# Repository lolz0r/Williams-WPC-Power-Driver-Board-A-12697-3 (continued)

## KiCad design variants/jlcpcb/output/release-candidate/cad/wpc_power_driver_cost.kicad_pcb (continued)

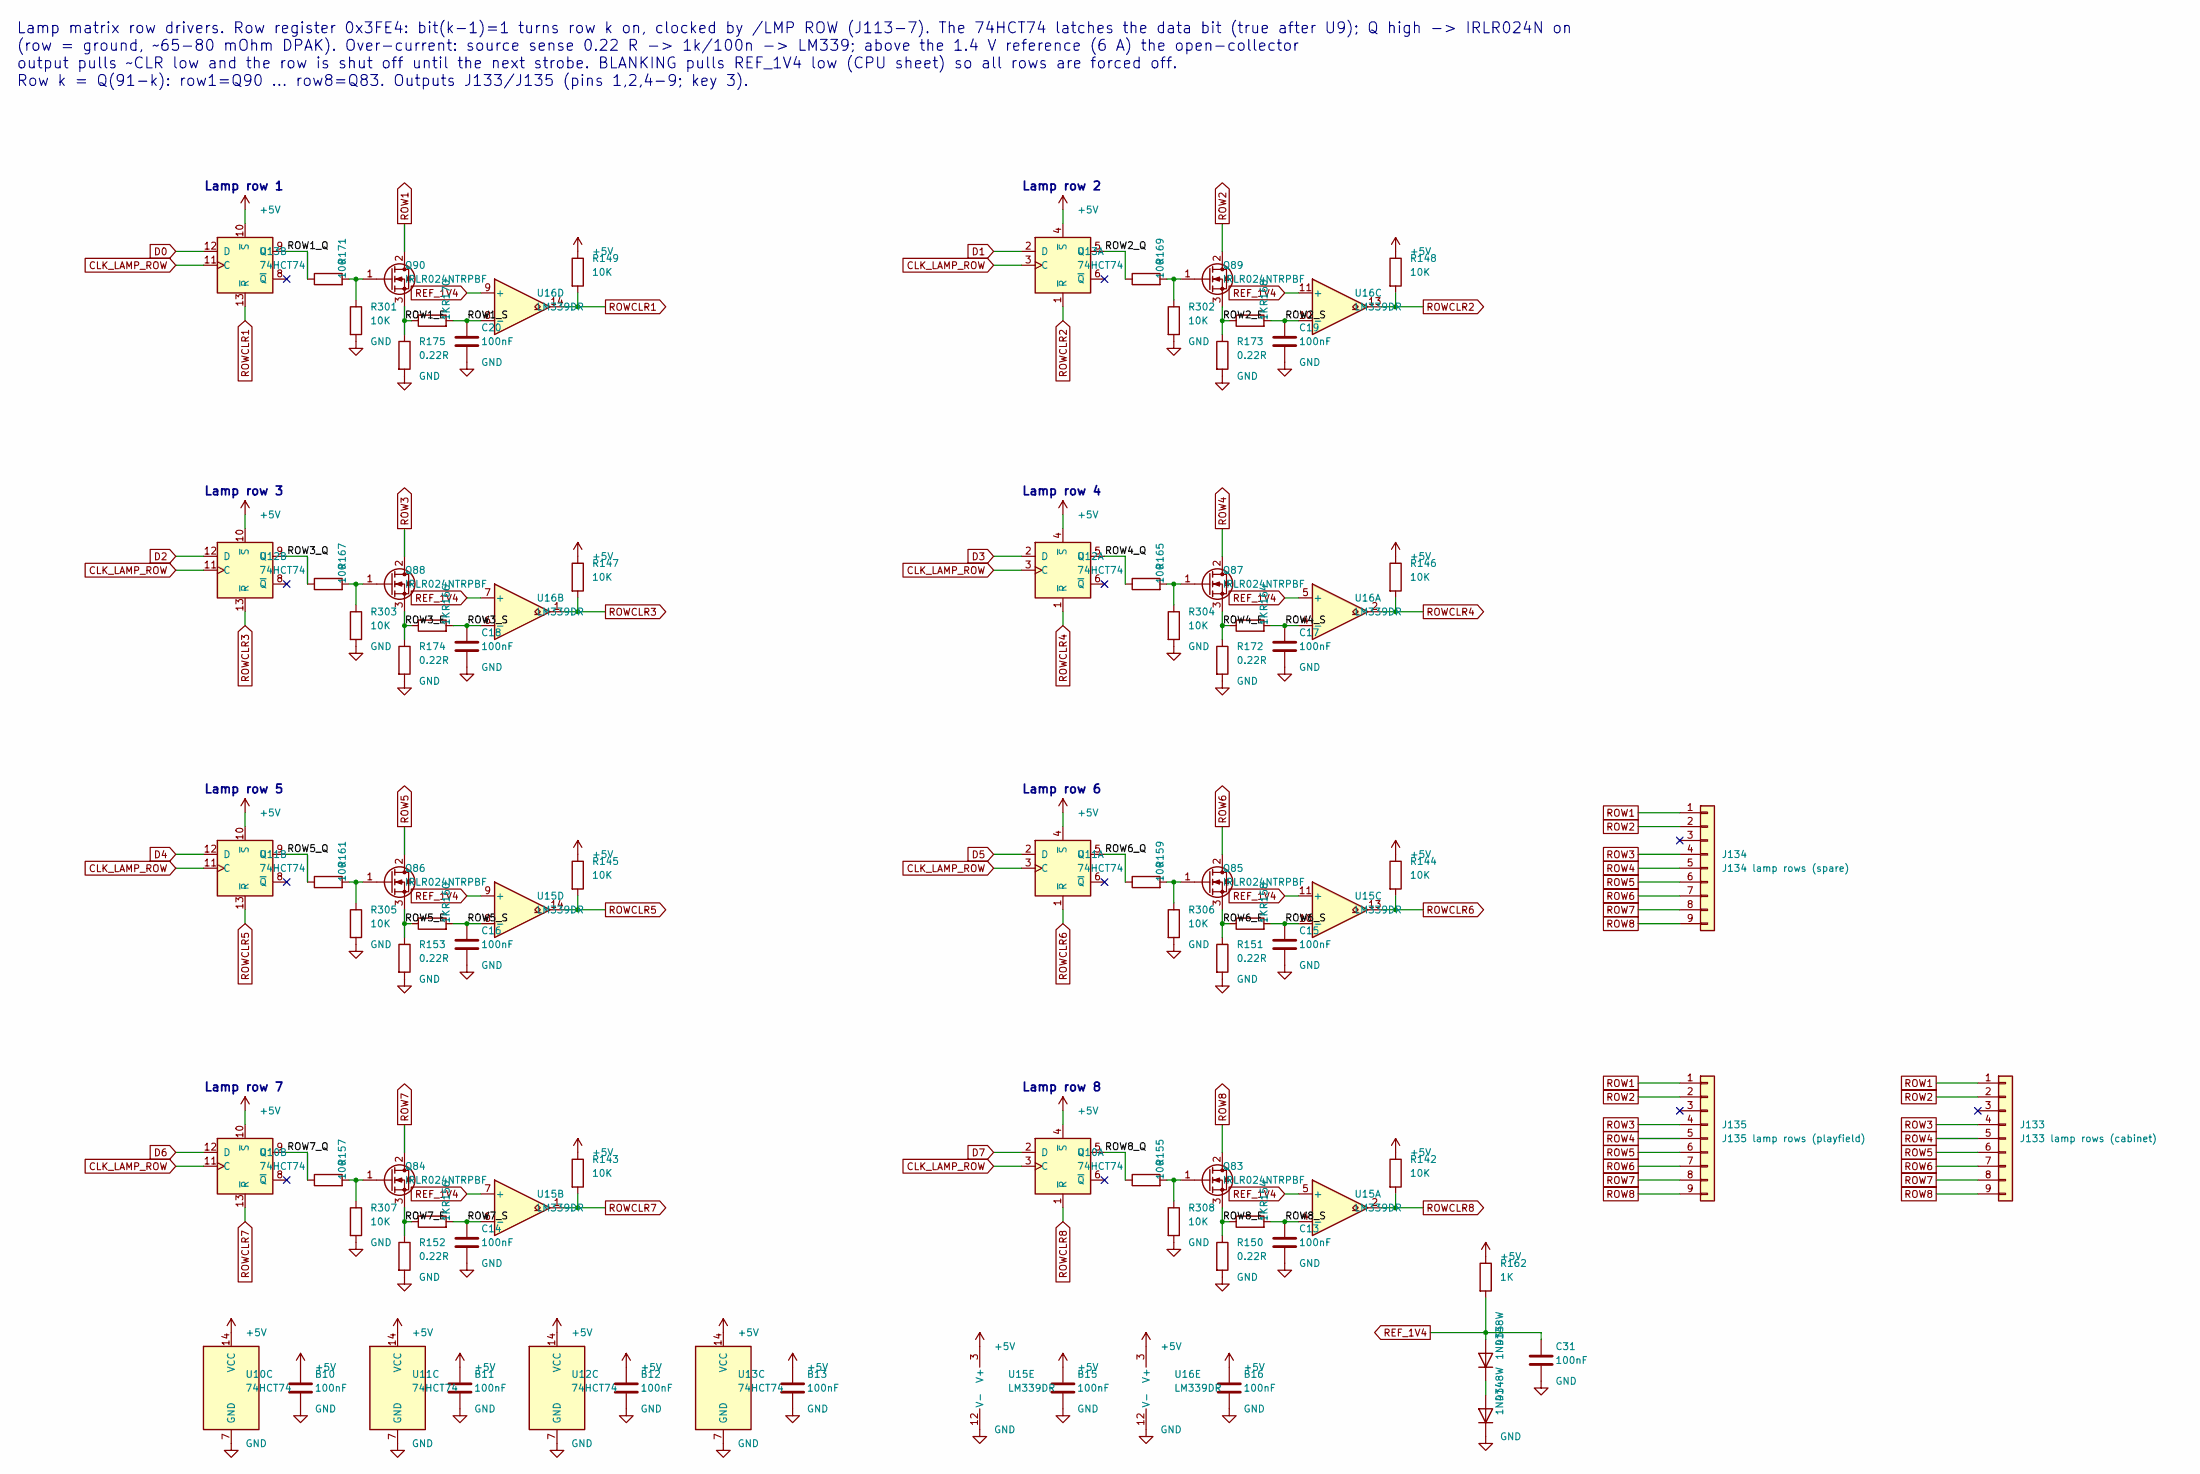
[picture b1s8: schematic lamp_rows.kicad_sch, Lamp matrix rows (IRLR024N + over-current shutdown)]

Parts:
B10, B11, B12, B13, B15, B16: 100nF; C_0805_2012Metric; MPN CC0805KRX7R9BB104; JLCPCB Part C49678
C13, C14, C15, C16, C17, C18, C19, C20, C31: 100nF; C_0805_2012Metric; MPN CC0805KRX7R9BB104; JLCPCB Part C49678
D33, D34: 1N4148W; D_SOD-123; MPN 1N4148W; JLCPCB Part C81598
J133: J133 lamp rows (cabinet); Molex_KK-254_AE-6410-09A_1x09_P2.54mm_Vertical; MPN 22232091; JLCPCB Part C587032
J134: J134 lamp rows (spare); Molex_KK-254_AE-6410-09A_1x09_P2.54mm_Vertical; MPN 22232091; JLCPCB Part C587032
J135: J135 lamp rows (playfield); Molex_KK-254_AE-6410-09A_1x09_P2.54mm_Vertical; MPN 22232091; JLCPCB Part C587032
Q83, Q84, Q85, Q86, Q87, Q88, Q89, Q90: IRLR024NTRPBF; TO-252-2; MPN IRLR024NTRPBF; JLCPCB Part C3007
R142, R143, R144, R145, R146, R147, R148, R149, R301, R302, R303, R304, R305, R306, R307, R308: 10K; R_0805_2012Metric; MPN 0805W8F1002T5E; JLCPCB Part C17414
R150, R151, R152, R153, R172, R173, R174, R175: 0.22R; R_2512_6332Metric; MPN RL2512FK-070R22L; JLCPCB Part C705613
R154, R156, R158, R160, R162, R164, R166, R168, R170: 1K; R_0805_2012Metric; MPN 0805W8F1001T5E; JLCPCB Part C17513
R155, R157, R159, R161, R165, R167, R169, R171: 100; R_0805_2012Metric; MPN 0805W8F1000T5E; JLCPCB Part C17408
U10, U11, U12, U13: 74HCT74; SOIC-14_3.9x8.7mm_P1.27mm; MPN SN74HCT74DR; JLCPCB Part C352961
U15, U16: LM339DR; SOIC-14_3.9x8.7mm_P1.27mm; MPN LM339DR; JLCPCB Part C7948

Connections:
+5V: B10.1, B11.1, B12.1, B13.1, B15.1, B16.1, R142.1, R143.1, R144.1, R145.1, R146.1, R147.1, R148.1, R149.1, R162.1, U10.4 (~S), U10.10 (~S), U10.14 (VCC), U11.4 (~S), U11.10 (~S), U11.14 (VCC), U12.4 (~S), U12.10 (~S), U12.14 (VCC), U13.4 (~S), U13.10 (~S), U13.14 (VCC), U15.3 (V+), U16.3 (V+); also elsewhere on the board
/Lamp_Rows/ROW1_E: Q90.3 (S), R170.1, R175.1
/Lamp_Rows/ROW1_Q: R171.1, U13.9 (Q)
/Lamp_Rows/ROW1_S: C20.1, R170.2, U16.8 (-)
/Lamp_Rows/ROW2_E: Q89.3 (S), R168.1, R173.1
/Lamp_Rows/ROW2_Q: R169.1, U13.5 (Q)
/Lamp_Rows/ROW2_S: C19.1, R168.2, U16.10 (-)
/Lamp_Rows/ROW3_E: Q88.3 (S), R166.1, R174.1
/Lamp_Rows/ROW3_Q: R167.1, U12.9 (Q)
/Lamp_Rows/ROW3_S: C18.1, R166.2, U16.6 (-)
/Lamp_Rows/ROW4_E: Q87.3 (S), R164.1, R172.1
/Lamp_Rows/ROW4_Q: R165.1, U12.5 (Q)
/Lamp_Rows/ROW4_S: C17.1, R164.2, U16.4 (-)
/Lamp_Rows/ROW5_E: Q86.3 (S), R153.1, R160.1
/Lamp_Rows/ROW5_Q: R161.1, U11.9 (Q)
/Lamp_Rows/ROW5_S: C16.1, R160.2, U15.8 (-)
/Lamp_Rows/ROW6_E: Q85.3 (S), R151.1, R158.1
/Lamp_Rows/ROW6_Q: R159.1, U11.5 (Q)
/Lamp_Rows/ROW6_S: C15.1, R158.2, U15.10 (-)
/Lamp_Rows/ROW7_E: Q84.3 (S), R152.1, R156.1
/Lamp_Rows/ROW7_Q: R157.1, U10.9 (Q)
/Lamp_Rows/ROW7_S: C14.1, R156.2, U15.6 (-)
/Lamp_Rows/ROW8_E: Q83.3 (S), R150.1, R154.1
/Lamp_Rows/ROW8_Q: R155.1, U10.5 (Q)
/Lamp_Rows/ROW8_S: C13.1, R154.2, U15.4 (-)
CLK_LAMP_ROW: U10.3 (C), U10.11 (C), U11.3 (C), U11.11 (C), U12.3 (C), U12.11 (C), U13.3 (C), U13.11 (C); also elsewhere on the board
D0: U13.12 (D); also elsewhere on the board
D1: U13.2 (D); also elsewhere on the board
D2: U12.12 (D); also elsewhere on the board
D3: U12.2 (D); also elsewhere on the board
D4: U11.12 (D); also elsewhere on the board
D5: U11.2 (D); also elsewhere on the board
D6: U10.12 (D); also elsewhere on the board
D7: U10.2 (D); also elsewhere on the board
unnamed: D33.1 (K), D34.2 (A)
unnamed: Q83.1 (G), R155.2, R308.1
unnamed: Q84.1 (G), R157.2, R307.1
unnamed: Q85.1 (G), R159.2, R306.1
unnamed: Q86.1 (G), R161.2, R305.1
unnamed: Q87.1 (G), R165.2, R304.1
unnamed: Q88.1 (G), R167.2, R303.1
unnamed: Q89.1 (G), R169.2, R302.1
unnamed: Q90.1 (G), R171.2, R301.1
REF_1V4: C31.1, D33.2 (A), R162.2, U15.5 (+), U15.7 (+), U15.9 (+), U15.11 (+), U16.5 (+), U16.7 (+), U16.9 (+), U16.11 (+); also elsewhere on the board
ROW1: J133.1, J134.1, J135.1, Q90.2 (D)
ROW2: J133.2, J134.2, J135.2, Q89.2 (D)
ROW3: J133.4, J134.4, J135.4, Q88.2 (D)
ROW4: J133.5, J134.5, J135.5, Q87.2 (D)
ROW5: J133.6, J134.6, J135.6, Q86.2 (D)
ROW6: J133.7, J134.7, J135.7, Q85.2 (D)
ROW7: J133.8, J134.8, J135.8, Q84.2 (D)
ROW8: J133.9, J134.9, J135.9, Q83.2 (D)
ROWCLR1: R149.2, U13.13 (~R), U16.14
ROWCLR2: R148.2, U13.1 (~R), U16.13
ROWCLR3: R147.2, U12.13 (~R), U16.1
ROWCLR4: R146.2, U12.1 (~R), U16.2
ROWCLR5: R145.2, U11.13 (~R), U15.14
ROWCLR6: R144.2, U11.1 (~R), U15.13
ROWCLR7: R143.2, U10.13 (~R), U15.1
ROWCLR8: R142.2, U10.1 (~R), U15.2

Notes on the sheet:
Lamp row 1
Lamp row 2
Lamp row 3
Lamp row 4
Lamp row 5
Lamp row 6
Lamp row 7
Lamp row 8
Lamp matrix row drivers. Row register 0x3FE4: bit(k-1)=1 turns row k on, clocked by /LMP ROW (J113-7). The 74HCT74 latches the data bit (true after U9); Q high -> IRLR024N on (row = ground, ~65-80 mOhm DPAK). Over-current: source sense 0.22 R -> 1k/100n -> LM339; above the 1.4 V reference (6 A) the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

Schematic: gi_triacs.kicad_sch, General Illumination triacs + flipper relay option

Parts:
B1: 100nF; C_0805_2012Metric; MPN CC0805KRX7R9BB104; JLCPCB Part C49678
D35: S1M (DNP); D_SMA; MPN S1M-13-F; not fitted
F101, F102: no fuse (clips only); Fuseholder_Clip-5x20mm_Keystone_3517_Inline_P23.11x6.76mm_D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; MPN 3517; JLCPCB Part C3029536
F106, F107, F108, F109, F110: 5A S.B.; Fuseholder_Clip-5x20mm_Keystone_3517_Inline_P23.11x6.76mm_D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; MPN 0239005.MXP; JLCPCB Part C151086
J105: J105 fused 51VAC (F112, pins 1/2) and fused 16VAC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; Molex_KK-396_A-41791-0005_1x05_P3.96mm_Vertical; MPN 26604050; JLCPCB Part C505166
J115: J115 G.I. 6.3VAC from transformer: 2-6 string hot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; Molex_KK-396_A-41791-0012_1x12_P3.96mm_Vertical; MPN 26-60-4120; JLCPCB Part C7426778
J119: J119 G.I. coin door (string 5); Molex_KK-396_A-41791-0003_1x03_P3.96mm_Vertical; MPN 26604030; JLCPCB Part C240823
J120: J120 G.I. strings 1-5 (backbox harness uses strin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; Molex_KK-396_A-41791-0011_1x11_P3.96mm_Vertical; MPN 26604110; JLCPCB Part C17541501
J121: J121 G.I. strings 1-5 (playfield harness uses str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; Molex_KK-396_A-41791-0011_1x11_P3.96mm_Vertical; MPN 26604110; JLCPCB Part C17541501
Q3: IPD90N10S4L06ATMA1; TO-252-2; MPN IPD90N10S4L06ATMA1; not fitted
Q9, Q11, Q13, Q15, Q17: MMBT4401; SOT-23; MPN MMBT4401-7-F; JLCPCB Part C151826
Q10, Q12, Q14, Q16, Q18: BTA16-600CRG; TO-220-3_Vertical; MPN BTA16-600CRG; JLCPCB Part C39797
R7, R10, R13, R16, R19: 27; R_2512_6332Metric; MPN RC2512JK-0727RL; JLCPCB Part C1882619
R8, R11, R14, R17, R20: 470; R_0805_2012Metric; MPN 0805W8F4700T5E; JLCPCB Part C17710
R9, R12, R15, R18, R21: 10K; R_0805_2012Metric; MPN 0805W8F1002T5E; JLCPCB Part C17414
R202: 100 (DNP); R_0805_2012Metric; MPN RC0805FR-07100RL; not fitted
R209: 10K (DNP); R_0805_2012Metric; MPN RC0805FR-0710KL; not fitted
RLY1: G2RL-2 12V (DNP); Relay_DPDT_Omron_G2RL-2; MPN G2RL-2 DC12; not fitted
U1: 74HCT574; SOIC-20W_7.5x12.8mm_P1.27mm; MPN SN74HCT574DWR; JLCPCB Part C6788
W1: 0R; R_2512_6332Metric; MPN RC2512JK-070RL; JLCPCB Part C189505

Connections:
+5V: B1.1, Q9.3 (C), Q11.3 (C), Q13.3 (C), Q15.3 (C), Q17.3 (C), U1.20 (VCC); also elsewhere on the board
+12V: D35.1 (K), RLY1.A1; also elsewhere on the board
/GI_Triacs/GI1_G: Q18.3 (G), R19.2
/GI_Triacs/GI2_G: Q10.3 (G), R7.2
/GI_Triacs/GI3_G: Q14.3 (G), R13.2
/GI_Triacs/GI4_G: Q16.3 (G), R16.2
/GI_Triacs/GI5_G: Q12.3 (G), R10.2
/GI_Triacs/RLY_COIL: D35.2 (A), Q3.2 (D), RLY1.A2
AC16_A_F: J105.4; also elsewhere on the board
AC16_B: J105.5; also elsewhere on the board
ACSOL_A: RLY1.11, RLY1.21; also elsewhere on the board
ACSOL_A_F: J105.1; also elsewhere on the board
ACSOL_B: J105.2; also elsewhere on the board
BLANKING: U1.1 (OE); also elsewhere on the board
CLK_GI: U1.11 (Cp); also elsewhere on the board
D0: U1.2 (D0); also elsewhere on the board
D1: U1.3 (D1); also elsewhere on the board
D2: U1.4 (D2); also elsewhere on the board
D3: U1.5 (D3); also elsewhere on the board
D4: U1.6 (D4); also elsewhere on the board
D5: U1.7 (D5); also elsewhere on the board
D6: U1.8 (D6); also elsewhere on the board
D7: U1.9 (D7); also elsewhere on the board
FLIP_RLY_L: R202.1, U1.12 (Q7); also elsewhere on the board
GI1_IN: F110.1, J115.2
GI1_L: R20.1, U1.19 (Q0)
GI1_OUT: F110.2, J120.7, J121.7
GI1_RET: J120.1, J121.1, Q18.2 (A2)
GI2_IN: F109.1, J115.4
GI2_L: R8.1, U1.18 (Q1)
GI2_OUT: F109.2, J120.8, J121.8
GI2_RET: J120.2, J121.2, Q10.2 (A2)
GI3_IN: F108.1, J115.5
GI3_L: R14.1, U1.17 (Q2)
GI3_OUT: F108.2, J120.9, J121.9
GI3_RET: J120.3, J121.3, Q14.2 (A2)
GI4_IN: F107.1, J115.3
GI4_L: R17.1, U1.16 (Q3)
GI4_OUT: F107.2, J120.10, J121.10
GI4_RET: J120.5, J121.5, Q16.2 (A2)
GI5_IN: F106.1, J115.6
GI5_L: R11.1, U1.15 (Q4)
GI5_OUT: F106.2, J119.1, J120.11, J121.11
GI5_RET: J119.3, J120.6, J121.6, Q12.2 (A2)
GI_BIT5: U1.14 (Q5); also elsewhere on the board
GI_BIT6: U1.13 (Q6); also elsewhere on the board
GI_RET: J115.7, J115.8, J115.10, J115.11, J115.12, Q10.1 (A1), Q12.1 (A1), Q14.1 (A1), Q16.1 (A1), Q18.1 (A1), W1.1
unnamed: F101.2, RLY1.14
unnamed: F102.2, RLY1.24
unnamed: Q3.1 (G), R202.2, R209.1
unnamed: Q9.1 (B), R8.2, R9.1
unnamed: Q9.2 (E), R7.1
unnamed: Q11.1 (B), R11.2, R12.1
unnamed: Q11.2 (E), R10.1
unnamed: Q13.1 (B), R14.2, R15.1
unnamed: Q13.2 (E), R13.1
unnamed: Q15.1 (B), R17.2, R18.1
unnamed: Q15.2 (E), R16.1
unnamed: Q17.1 (B), R20.2, R21.1
unnamed: Q17.2 (E), R19.1

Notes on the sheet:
G.I. string #1 (Wht-Brn / Brn)
G.I. string #2 (Wht-Org / Org)
G.I. string #3 (Wht-Yel / Yel)
G.I. string #4 (Wht-Grn / Grn)
G.I. string #5 (Wht-Vio / Vio)
General illumination: each 6.3VAC string is fused (F106-F110) on the hot side and switched by a triac in the RETURN path; MT1 of the five triacs form the GI_RET bus that goes back to the transformer on J115-7/8/10/11/12 and is referenced to logic ground by W1 (OEM: J115-1 GND REF), so the 5 x 5 A r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

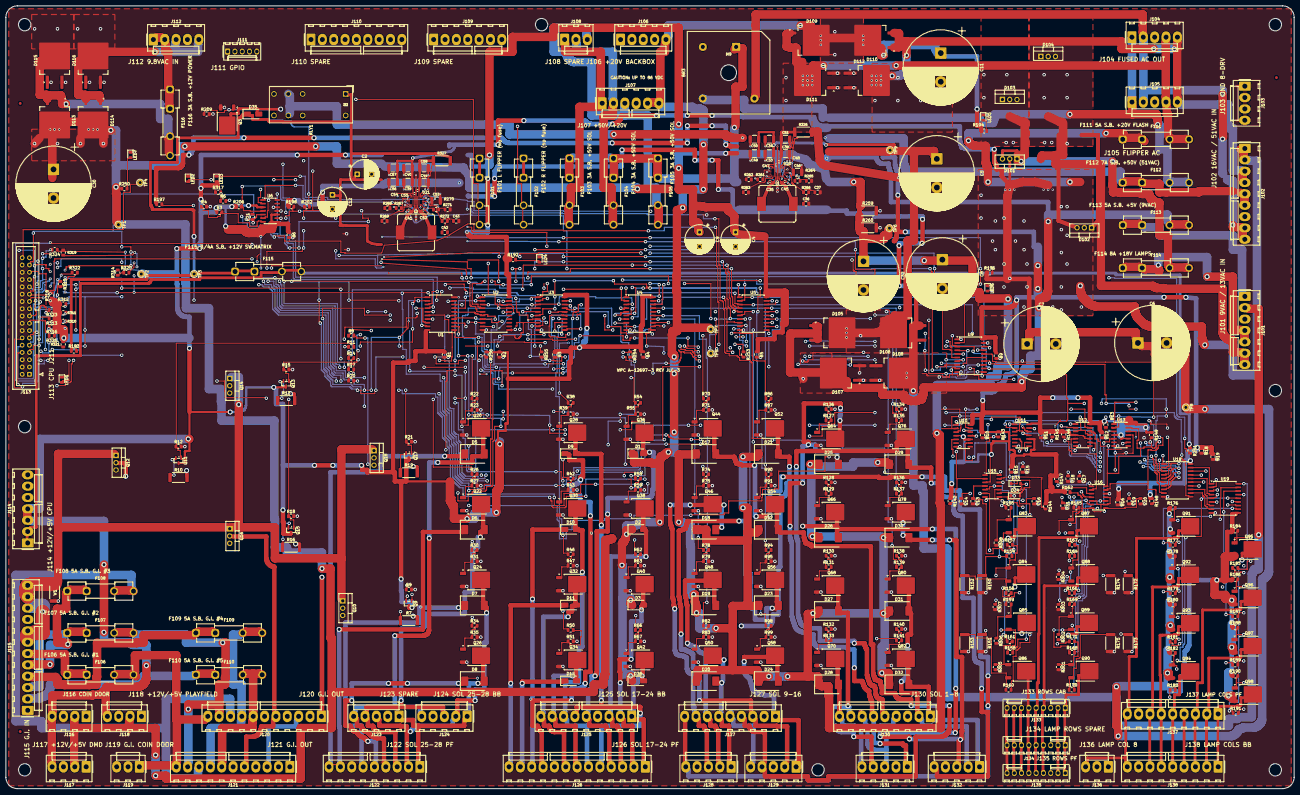
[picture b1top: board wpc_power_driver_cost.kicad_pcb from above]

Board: 4 copper layers, 449.2 x 272.9 mm, 446 parts (0 on the bottom side), 294 nets.

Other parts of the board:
FID1, FID2, FID3: FIDUCIAL; Fiducial_1mm_Mask2mm
H9: BR3 M4 bolt; MountingHole_5.5mm

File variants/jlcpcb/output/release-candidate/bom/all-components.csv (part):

Refs,Qty,Value,Footprint,Manufacturer,MPN,Description,Link,DNP
BR3,1,GBPC3510,Diode_THT:Diode_Bridge_28.6x28.6x7.3mm_P18.0mm_P11.6mm,Vishay Intertech,GBPC3510W-E4/51,"Bridge rectifier 35 A 1000 V, GBPC-W (28.6 mm square block, wire leads, #10 centre hole, metal base up when PCB-mounted)",https://jlcpcb.com/partdetail/VishayIntertech-GBPC3510W_E451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,
C2,1,330uF,wpc_cost:CP_Radial_D8.0mm_P5.00mm,PANASONIC,EEU-FR1E331B,Output capacitor 330 uF 25 V low ESR,https://jlcpcb.com/partdetail/PANASONIC-EEUFR1E331B/C1579638,
C4,1,330uF,wpc_cost:CP_Radial_D8.0mm_P5.00mm,PANASONIC,EEU-FR1E331B,Output capacitor 330 uF 25 V low ESR,https://jlcpcb.com/partdetail/PANASONIC-EEUFR1E331B/C1579638,
C5,1,10000uF 35V,Capacitor_THT:CP_Radial_D26.0mm_P10.00mm_SnapIn,TDK,B41252A7109M000,"Capacitor 10000 uF 35 V snap-in 25.4x45 mm, 10 mm pitch, 6.0 mm leads, PVC sleeve, 105C; permissible ripple 7.89 A at 60C / 120 Hz; local ambient <=60C design condition",https://jlcpcb.com/partdetail/TDK-B41252A7109M000/C6130373,
C6,1,10000uF 35V,Capacitor_THT:CP_Radial_D26.0mm_P10.00mm_SnapIn,TDK,B41252A7109M000,"Capacitor 10000 uF 35 V snap-in 25.4x45 mm, 10 mm pitch, 6.0 mm leads, PVC sleeve, 105C; permissible ripple 7.89 A at 60C / 120 Hz; local ambient <=60C design condition",https://jlcpcb.com/partdetail/TDK-B41252A7109M000/C6130373,
C7,1,10000uF 35V,Capacitor_THT:CP_Radial_D26.0mm_P10.00mm_SnapIn,TDK,B41252A7109M000,"Capacitor 10000 uF 35 V snap-in 25.4x45 mm, 10 mm pitch, 6.0 mm leads, PVC sleeve, 105C; permissible ripple 7.89 A at 60C / 120 Hz; local ambient <=60C design condition",https://jlcpcb.com/partdetail/TDK-B41252A7109M000/C6130373,
C8,1,2200uF 100V,Capacitor_THT:CP_Radial_D25.0mm_P10.00mm_SnapIn,Nichicon,LLS2A222MELA,Capacitor 2200 uF 100 V snap-in 25x40 mm,https://jlcpcb.com/partdetail/Nichicon-LLS2A222MELA/C1582025,
C9,1,330uF,wpc_cost:CP_Radial_D8.0mm_P5.00mm,PANASONIC,EEU-FR1E331B,Output capacitor 330 uF 25 V low ESR,https://jlcpcb.com/partdetail/PANASONIC-EEUFR1E331B/C1579638,
C11,1,10000uF 35V,Capacitor_THT:CP_Radial_D26.0mm_P10.00mm_SnapIn,TDK,B41252A7109M000,"Capacitor 10000 uF 35 V snap-in 25.4x45 mm, 10 mm pitch, 6.0 mm leads, PVC sleeve, 105C; permissible ripple 7.89 A at 60C / 120 Hz; local ambient <=60C design condition",https://jlcpcb.com/partdetail/TDK-B41252A7109M000/C6130373,
C12,1,330uF,wpc_cost:CP_Radial_D8.0mm_P5.00mm,PANASONIC,EEU-FR1E331B,Output capacitor 330 uF 25 V low ESR,https://jlcpcb.com/partdetail/PANASONIC-EEUFR1E331B/C1579638,
C30,1,10000uF 35V,Capacitor_THT:CP_Radial_D26.0mm_P10.00mm_SnapIn,TDK,B41252A7109M000,"Capacitor 10000 uF 35 V snap-in 25.4x45 mm, 10 mm pitch, 6.0 mm leads, PVC sleeve, 105C; permissible ripple 7.89 A at 60C / 120 Hz; local ambient <=60C design condition",https://jlcpcb.com/partdetail/TDK-B41252A7109M000/C6130373,
C32,1,2200uF 100V,Capacitor_THT:CP_Radial_D25.0mm_P10.00mm_SnapIn,Nichicon,LLS2A222MELA,Capacitor 2200 uF 100 V snap-in 25x40 mm,https://jlcpcb.com/partdetail/Nichicon-LLS2A222MELA/C1582025,
C33,1,10uF,Capacitor_SMD:C_1210_3225Metric,Samsung Electro-Mechanics,CL32B106KBJNNWE,10 uF 50 V X7R input bypass; four parallel capacitors,https://jlcpcb.com/partdetail/4412651-CL32B106KBJNNWE/C3844168,
C34,1,10uF,Capacitor_SMD:C_1210_3225Metric,Samsung Electro-Mechanics,CL32B106KBJNNWE,10 uF 50 V X7R input bypass; four parallel capacitors,https://jlcpcb.com/partdetail/4412651-CL32B106KBJNNWE/C3844168,
C35,1,100nF,Capacitor_SMD:C_0402_1005Metric,Murata Electronics,GRM155R71H104KE14D,100 nF 50 V X7R; short local bootstrap / high-frequency loop,https://jlcpcb.com/partdetail/C77020,
C36,1,100nF,Capacitor_SMD:C_0805_2012Metric,YAGEO,CC0805KRX7R9BB104,TPS552892 compensation series capacitor; TI equation 25,https://jlcpcb.com/partdetail/C49678,
C37,1,680pF,Capacitor_SMD:C_0805_2012Metric,YAGEO,CC0805JRNPO9BN681,TPS552892 compensation high-frequency pole capacitor; C0G; TI equation 26,https://jlcpcb.com/partdetail/C107121,
C38,1,10uF,Capacitor_SMD:C_1210_3225Metric,Samsung Electro-Mechanics,CL32B106KBJNNWE,"10 uF 50 V X7R local output bypass, before current sense",https://jlcpcb.com/partdetail/4412651-CL32B106KBJNNWE/C3844168,
C39,1,10uF,Capacitor_SMD:C_1210_3225Metric,Samsung Electro-Mechanics,CL32B106KBJNNWE,10 uF 50 V X7R input bypass; four parallel capacitors,https://jlcpcb.com/partdetail/4412651-CL32B106KBJNNWE/C3844168,
C40,1,10uF,Capacitor_SMD:C_1210_3225Metric,Samsung Electro-Mechanics,CL32B106KBJNNWE,10 uF 50 V X7R input bypass; four parallel capacitors,https://jlcpcb.com/partdetail/4412651-CL32B106KBJNNWE/C3844168,
C41,1,100nF,Capacitor_SMD:C_0402_1005Metric,Murata Electronics,GRM155R71H104KE14D,100 nF 50 V X7R; short local bootstrap / high-frequency loop,https://jlcpcb.com/partdetail/C77020,
C42,1,330nF,Capacitor_SMD:C_0805_2012Metric,Samsung Electro-Mechanics,CL21B334KBFNNNE,TPS552892 compensation series capacitor; TI equation 25,https://jlcpcb.com/partdetail/C73142,
C43,1,1nF,Capacitor_SMD:C_0805_2012Metric,YAGEO,CC0805JRNPO9BN102,TPS552892 compensation high-frequency pole capacitor; C0G; TI equation 26,https://jlcpcb.com/partdetail/C62774,
C44,1,10uF,Capacitor_SMD:C_1210_3225Metric,Samsung Electro-Mechanics,CL32B106KBJNNWE,"10 uF 50 V X7R local output bypass, before current sense",https://jlcpcb.com/partdetail/4412651-CL32B106KBJNNWE/C3844168,
C45,1,100nF,Capacitor_SMD:C_0402_1005Metric,Murata Electronics,GRM155R71H104KE14D,100 nF 50 V X7R; short local bootstrap / high-frequency loop,https://jlcpcb.com/partdetail/C77020,
C46,1,10uF,Capacitor_SMD:C_1210_3225Metric,Samsung Electro-Mechanics,CL32B106KBJNNWE,10 uF 50 V X7R on internal 5.2 V VCC; >4.7 uF effective,https://jlcpcb.com/partdetail/4412651-CL32B106KBJNNWE/C3844168,
C47,1,100nF,Capacitor_SMD:C_0402_1005Metric,Murata Electronics,GRM155R71H104KE14D,100 nF 50 V X7R; short local bootstrap / high-frequency loop,https://jlcpcb.com/partdetail/C77020,
C48,1,100nF,Capacitor_SMD:C_0402_1005Metric,Murata Electronics,GRM155R71H104KE14D,100 nF 50 V X7R; short local bootstrap / high-frequency loop,https://jlcpcb.com/partdetail/C77020,
C49,1,10uF,Capacitor_SMD:C_1210_3225Metric,Samsung Electro-Mechanics,CL32B106KBJNNWE,10 uF 50 V X7R input bypass; four parallel capacitors,https://jlcpcb.com/partdetail/4412651-CL32B106KBJNNWE/C3844168,
C50,1,10uF,Capacitor_SMD:C_1210_3225Metric,Samsung Electro-Mechanics,CL32B106KBJNNWE,10 uF 50 V X7R input bypass; four parallel capacitors,https://jlcpcb.com/partdetail/4412651-CL32B106KBJNNWE/C3844168,
C51,1,10uF,Capacitor_SMD:C_1210_3225Metric,Samsung Electro-Mechanics,CL32B106KBJNNWE,"10 uF 50 V X7R local output bypass, before current sense",https://jlcpcb.com/partdetail/4412651-CL32B106KBJNNWE/C3844168,
C52,1,100nF,Capacitor_SMD:C_0402_1005Metric,Murata Electronics,GRM155R71H104KE14D,100 nF 50 V X7R; short local bootstrap / high-frequency loop,https://jlcpcb.com/partdetail/C77020,
C53,1,10uF,Capacitor_SMD:C_1210_3225Metric,Samsung Electro-Mechanics,CL32B106KBJNNWE,10 uF 50 V X7R on internal 5.2 V VCC; >4.7 uF effective,https://jlcpcb.com/partdetail/4412651-CL32B106KBJNNWE/C3844168,
C54,1,100nF,Capacitor_SMD:C_0402_1005Metric,Murata Electronics,GRM155R71H104KE14D,100 nF 50 V X7R; short local bootstrap / high-frequency loop,https://jlcpcb.com/partdetail/C77020,
C55,1,100nF,Capacitor_SMD:C_0402_1005Metric,Murata Electronics,GRM155R71H104KE14D,100 nF 50 V X7R; short local bootstrap / high-frequency loop,https://jlcpcb.com/partdetail/C77020,
C56,1,10uF,Capacitor_SMD:C_1210_3225Metric,Samsung Electro-Mechanics,CL32B106KBJNNWE,10 uF 50 V X7R input bypass; four parallel capacitors,https://jlcpcb.com/partdetail/4412651-CL32B106KBJNNWE/C3844168,
C57,1,10uF,Capacitor_SMD:C_1210_3225Metric,Samsung Electro-Mechanics,CL32B106KBJNNWE,10 uF 50 V X7R input bypass; four parallel capacitors,https://jlcpcb.com/partdetail/4412651-CL32B106KBJNNWE/C3844168,
C58,1,10uF,Capacitor_SMD:C_1210_3225Metric,Samsung Electro-Mechanics,CL32B106KBJNNWE,"10 uF 50 V X7R local output bypass, before current sense",https://jlcpcb.com/partdetail/4412651-CL32B106KBJNNWE/C3844168,
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
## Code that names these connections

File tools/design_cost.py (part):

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 * J104 carries the F112-fused 51 VAC leg (pins 1/2) and the F111-fused 16 VAC leg (pins 4/5) like the A-12697 (sheet 1), not the raw winding
 * +12 V: the regulated rail (U21, F115) comes from the +18 V lamp supply and only feeds J114 ("+12 V digital"); J116/J117/J118 pin 2 carry
   the UNREGULATED +12 V ("+12 V power": motors, optos, coin door, DMD) from BR5 (GBU8J) / C30 (10000 uF), fused by F116 as on the original
 * G.I.: triac MT1 terminals go to the transformer return pins of J115 (7, 8, 10, 11, 12) on a GI_RET net that is tied to logic ground by
   the 0 R link W1 (OEM: J115-1 "GND REF"), so the string return current does not flow through the logic ground plane
 * +50 V is really ~70 V DC (51 VAC winding): bleeder R259 || R260 (2 x 15 k, 2512), S3M tie-backs on sol 9-16 / 25-28 (PWM-held coils),
   TP6 = +50 V and TP8 = +18 V as on the factory schematic; J111 carries the G.I. latch spare bits T5-T7 (GPIO) as on the original
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        b.pin_net(ref, str(2 + i), ins[i], shape='input')
        b.pin_net(ref, str(19 - i), out_nets[i], shape='output')
    b.pin_net(ref, '11', clk_net, shape='input')
    b.pin_net(ref, '1', 'BLANKING', shape='input')
    b.pwr('+5V', b.pin(ref, '20')); b.gnd(b.pin(ref, '10'))

def bypass(b, ref, x, y):
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        fet_driver(b, ox, oy, n, q, rg, rpd, dio, 'IRLR3110Z', '+50V', f'SOL{n:02d}_L', f'SOL{n:02d}', 'high power', hp=True)
    latch574(b, 'U5', 60, 210, 'CLK_SOL_HIGH', [f'SOL{n:02d}_L' for n in range(1, 9)], desc='Solenoid 1-8 latch')
    bypass(b, 'B5', 110, 195)
    b.conn_labels('J130', 9, 300, 200, {1: 'SOL01', 2: 'SOL02', 3: None, 4: 'SOL03', 5: 'SOL04', 6: 'SOL05', 7: 'SOL06', 8: 'SOL07', 9: 'SOL08'},
                  FP_KK(9), 'KK9', 'J130 Sol 1-8 drive (playfield)')
    # J132 (B.B.) / J131 (CAB): 5-pin copies of J130 as on A-12697 sheet 3 (N/C in the STTNG harness) - docs/INTERFACE_PARITY.md
    b.conn_labels('J132', 5, 360, 200, {1: 'SOL01', 2: 'SOL02', 3: 'SOL03', 4: None, 5: 'SOL04'}, FP_KK(5), 'KK5', 'J132 Sol 1-4 drive (backbox, parallel to J130; N/C on STTNG)')
    b.conn_labels('J131', 5, 360, 235, {1: 'SOL05', 2: None, 3: 'SOL06', 4: 'SOL07', 5: 'SOL08'}, FP_KK(5), 'KK5', 'J131 Sol 5-8 drive (cabinet, parallel to J130; N/C on STTNG)')
    b.text('High power solenoid drivers (sol. 1-8): IRLR3110Z DPAK (100 V, 14 mOhm, 16 mOhm at 4.5 V) driven directly by latch U5 (74HCT574, output HIGH = ON,\n'
           'outputs tri-stated by BLANKING -> gate pull-downs hold every driver OFF). SMC 3 A tie-back diodes return to +50V (the "+50V" rail of a WPC\n'
           'machine is ~70 V DC: 51 VAC winding, 72-78 V peak). U5 is clocked by /SOL 4 (J113-10). Output connectors J130 (playfield, key pin 3), J132 (backbox, sol 1-4, key 4)\n'
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        fet_driver(b, ox, oy, n, fet='IRLR3110Z', tie_net='+50V', in_net=f'SOL{n:02d}_L', out_net=f'SOL{n:02d}', kind='low power', big_diode=True, **lp_parts(SOL_Q[n]))
    latch574(b, 'U4', 60, 200, 'CLK_SOL_LOW', [f'SOL{n:02d}_L' for n in range(9, 17)], desc='Solenoid 9-16 latch')
    bypass(b, 'B4', 110, 185)
    b.conn_labels('J127', 9, 300, 190, {1: 'SOL09', 2: None, 3: 'SOL10', 4: 'SOL11', 5: 'SOL12', 6: 'SOL13', 7: 'SOL14', 8: 'SOL15', 9: 'SOL16'},
                  FP_KK(9), 'KK9', 'J127 Sol 9-16 drive (playfield)')
    # J129 (B.B.) / J128 (CAB): 5-pin copies of J127 as on A-12697 sheet 3 (N/C in the STTNG harness) - docs/INTERFACE_PARITY.md
    b.conn_labels('J129', 5, 360, 190, {1: 'SOL09', 2: 'SOL10', 3: None, 4: 'SOL11', 5: 'SOL12'}, FP_KK(5), 'KK5', 'J129 Sol 9-12 drive (backbox, parallel to J127; N/C on STTNG)')
    b.conn_labels('J128', 5, 360, 225, {1: 'SOL13', 2: 'SOL14', 3: 'SOL15', 4: None, 5: 'SOL16'}, FP_KK(5), 'KK5', 'J128 Sol 13-16 drive (cabinet, parallel to J127; N/C on STTNG)')
    b.text('Low power solenoid drivers (sol. 9-16): IRLR3110Z logic-level DPAK MOSFETs (14 mOhm), latch U4 output HIGH = ON, clocked by /SOL 3 (J113-11).\n'
           'Tie-back diodes S3M (SMC, 3 A) to +50V (~70 V DC in the machine): coils in this group can be PWM-held by the firmware, the diode then carries the freewheel current.\n'
           'Output connectors J127 (playfield, key pin 2), J129 (backbox, sol 9-12, key 3) and J128 (cabinet, sol 13-16, key 4) as on the A-12697. Supply +50V via F104 on J107-2.', (20, 15), 2.0)
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        fet_driver(b, ox, oy, n, fet='IRLR3110Z', tie_net=(f'SOL{n:02d}_TB' if n >= 21 else '+20V'), in_net=f'SOL{n:02d}_L', out_net=f'SOL{n:02d}', kind='flasher', **lp_parts(SOL_Q[n]))
    latch574(b, 'U3', 60, 200, 'CLK_SOL_FLASH', [f'SOL{n:02d}_L' for n in range(17, 25)], desc='Solenoid 17-24 latch')
    bypass(b, 'B3', 110, 185)
    b.conn_labels('J126', 13, 300, 180, {1: 'SOL17', 2: 'SOL18', 3: 'SOL19', 4: 'SOL20', 5: 'SOL21', 6: 'SOL22', 7: 'SOL23', 8: 'SOL24',
                                         9: None, 10: 'SOL21_TB', 11: 'SOL22_TB', 12: 'SOL23_TB', 13: 'SOL24_TB'}, FP_KK(13), 'KK13',
                  'J126 Sol 17-24 drive (playfield flashers) + tie-back cathodes of sol 21-24 on pins 10-13 (A-12697 D9-D12; N/C on STTNG)')
    # J125 key = pin 4 (A-12697-1 silkscreen film, manual p.3-33 connector map and a photographed board all show the plug at position 4;
    # the 16-9057 schematic symbol draws the KEY at pin 5) -> sol 20 sits on pin 5; the STTNG harness only uses pins 6 (sol 21) and 8 (sol 23)
    b.conn_labels('J125', 9, 360, 180, {1: 'SOL17', 2: 'SOL18', 3: 'SOL19', 4: None, 5: 'SOL20', 6: 'SOL21', 7: 'SOL22', 8: 'SOL23', 9: 'SOL24'},
                  FP_KK(9), 'KK9', 'J125 Sol 17-24 drive (backbox flashers)')
    b.text('Flashlamp drivers (sol. 17-24): IRLR3110Z DPAK, latch U3 output HIGH = lamp ON, clocked by /SOL 2 (J113-9). Sol 17-20 keep an on-board S1M tie-back to +20V\n'
           '(the A-12697 has none there); the sol 21-24 tie-back cathodes are brought out to J126-10..13 exactly like the A-12697 D9-D12, so the harness chooses the clamp rail.\n'
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        fet_driver(b, ox, oy, n, fet='IRLR3110Z', tie_net=f'SOL{n:02d}_TB', in_net=f'SOL{n:02d}_L', out_net=f'SOL{n:02d}', kind='gen. purpose', big_diode=True, **lp_parts(SOL_Q[n]))
    latch574(b, 'U2', 60, 150, 'CLK_SOL_GEN', [f'SOL{n:02d}_L' for n in range(25, 29)] + [None] * 4, desc='Solenoid 25-28 latch')
    bypass(b, 'B2', 110, 135)
    b.conn_labels('J122', 9, 300, 140, {1: 'SOL25', 2: 'SOL26', 3: 'SOL27', 4: 'SOL28', 5: 'SOL25_TB', 6: 'SOL26_TB', 7: None, 8: 'SOL27_TB', 9: 'SOL28_TB'},
                  FP_KK(9), 'KK9', 'J122 Sol 25-28 drive + tie-back (playfield)')
    b.conn_labels('J124', 5, 360, 140, {1: 'SOL25', 2: 'SOL26', 3: 'SOL27', 4: None, 5: 'SOL28'}, FP_KK(5), 'KK5', 'J124 Sol 25-28 drive (backbox)')
    # J123 (B.B.): sol 25-28 with the key on pin 2 (A-12697 sheet 3 + silkscreen film); N/C in the STTNG harness
    b.conn_labels('J123', 5, 360, 190, {1: 'SOL25', 2: None, 3: 'SOL26', 4: 'SOL27', 5: 'SOL28'}, FP_KK(5), 'KK5', 'J123 Sol 25-28 drive (backbox, parallel to J122/J124; N/C on STTNG)')
    b.text('General purpose drivers (sol. 25-28): IRLR3110Z DPAK, latch U2 output HIGH = ON, clocked by /SOL 1 (J113-12). S3M tie-back diode cathodes are brought out\n'
           'to J122 pins 5,6,8,9 so the harness can tie them to the supply actually used (+50V coil or +20V flasher).\n'
           'Outputs J122 (playfield, key pin 7), J123 (backbox, key pin 2) and J124 (cabinet, key pin 4) as on the A-12697. U2 bits 4-7 unused.', (20, 15), 2.0)
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    top = b.pin(rpd, 1); b.w(top, (top[0], pB[1])); b.j((top[0], pB[1])); b.gnd(b.pin(rpd, 2))
    b.gl(f'GI{n}_L', b.pin(rb, 1), 180, 'input')
    b.lbl(f'GI{n}_G', g)
    b.w(a1, (a1[0], a1[1] + 5.08)); b.gl('GI_RET', (a1[0], a1[1] + 5.08), 270, 'passive')     # MT1 -> transformer return pins (J115), not the logic ground
    b.w(a2, (a2[0], a2[1] - 5.08)); b.gl(f'GI{n}_RET', (a2[0], a2[1] - 5.08), 90, 'input')
    fa, fb = b.pin(fuse, 1), b.pin(fuse, 2)
    b.w(fa, (fa[0], fa[1] - 2.54)); b.gl(f'GI{n}_IN', (fa[0], fa[1] - 2.54), 90, 'input')
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        gi_driver(b, 60 + i * 85, 60, n)
    latch574(b, 'U1', 60, 150, 'CLK_GI', ['GI1_L', 'GI2_L', 'GI3_L', 'GI4_L', 'GI5_L', 'GI_BIT5', 'GI_BIT6', 'FLIP_RLY_L'], desc='G.I. / relay latch')
    bypass(b, 'B1', 110, 135)
    b.conn_labels('J115', 12, 300, 140, {1: 'GND', 2: 'GI1_IN', 3: 'GI4_IN', 4: 'GI2_IN', 5: 'GI3_IN', 6: 'GI5_IN', 7: 'GI_RET', 8: 'GI_RET', 9: None, 10: 'GI_RET', 11: 'GI_RET', 12: 'GI_RET'},
                  FP_KK(12), 'KK12', 'J115 G.I. 6.3VAC from transformer: 2-6 string hot ends (one fuse each), 7/8/10/11/12 winding return ends (triac MT1), 1 = GND REF')
    b.two('W1', R, 240, 190, '0R', FP_R2512, r2512('0R'), 'GI_RET', 'GND', desc='0 R link 2512: G.I. return bus (triac MT1 / J115 returns) to the logic ground reference (OEM: J115-1 GND REF at the transformer)')
    # J120 (PLFD) and J121 (B.B.) are wired in parallel on the A-12697 (sheet 1): all five strings on both, 7-11 hot / 1,2,3,5,6 return, key 4.
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    GI11 = {1: 'GI1_RET', 2: 'GI2_RET', 3: 'GI3_RET', 4: None, 5: 'GI4_RET', 6: 'GI5_RET', 7: 'GI1_OUT', 8: 'GI2_OUT', 9: 'GI3_OUT', 10: 'GI4_OUT', 11: 'GI5_OUT'}
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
